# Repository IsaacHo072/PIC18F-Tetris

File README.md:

# PIC18F-Tetris
Tetris game which runs on a PIC18

## Hardware
- PIC18F4520
- HT16K33
- 8x8 Bi-Colour Common-Cathode LED Matrix
- 13mm Seven Segment Display, Common-Cathode
- 74HC14
- Some cherry-mx compatible switches

## Program
- Button polling used to read the buttons
- simpletetris.c is the main game program, also directly write to the displays
- Device configuration code in devcon.h

## Tetris
Has basic Tetris features including moving left, right, down and rotating the piece.
Also for holding one Tetris piece in top-left corner. Top-right corner shows the next piece to be dropped.

## Compiling
The program could be compiled with the legacy MPLAB C18 C Complier. 
Change the device configuration and I2C function to I2C1/2 if a different PIC18 microcontroller is used.

## Pictures

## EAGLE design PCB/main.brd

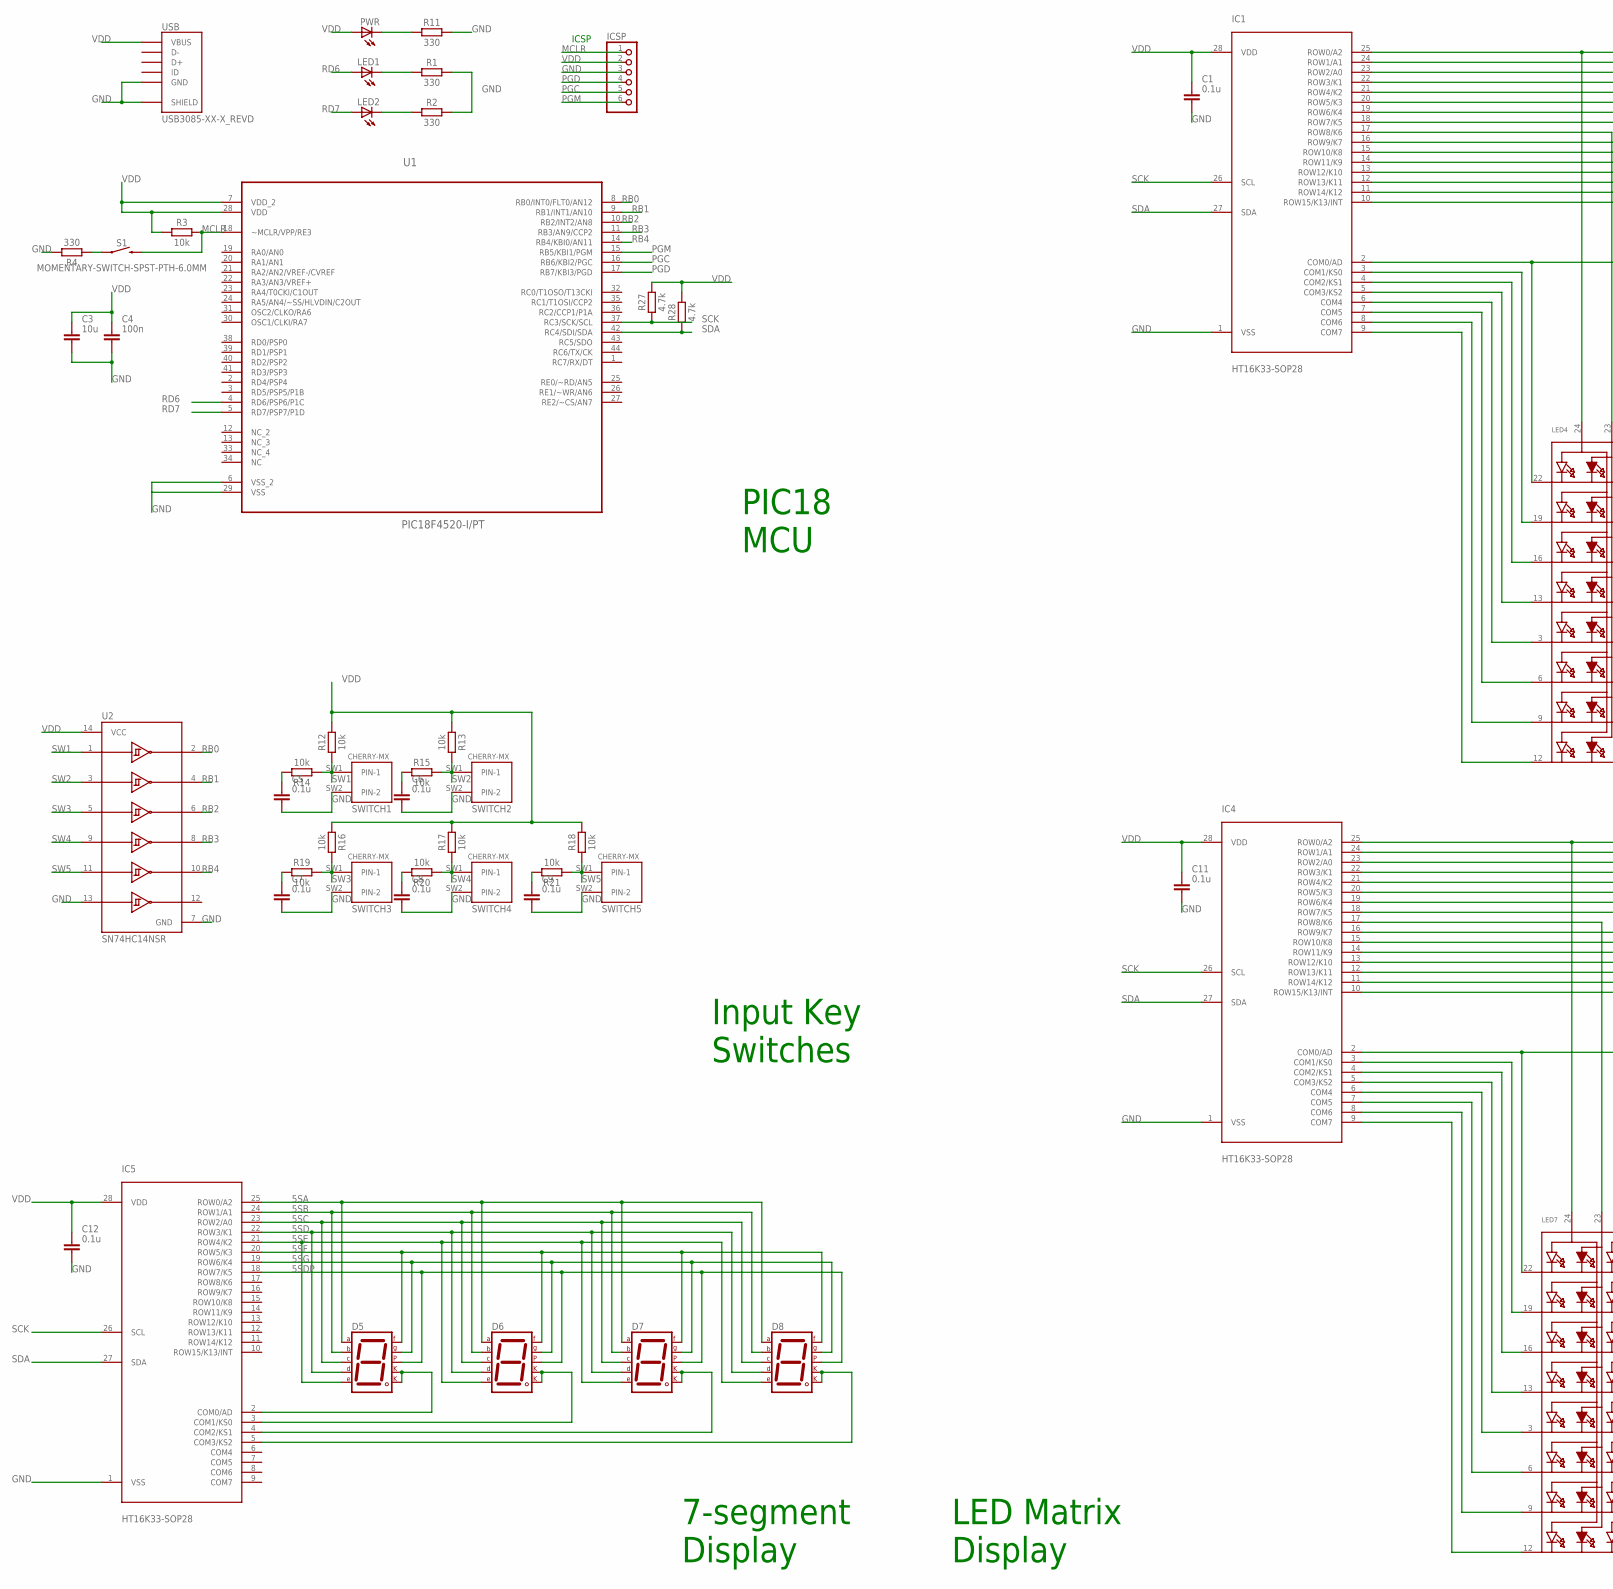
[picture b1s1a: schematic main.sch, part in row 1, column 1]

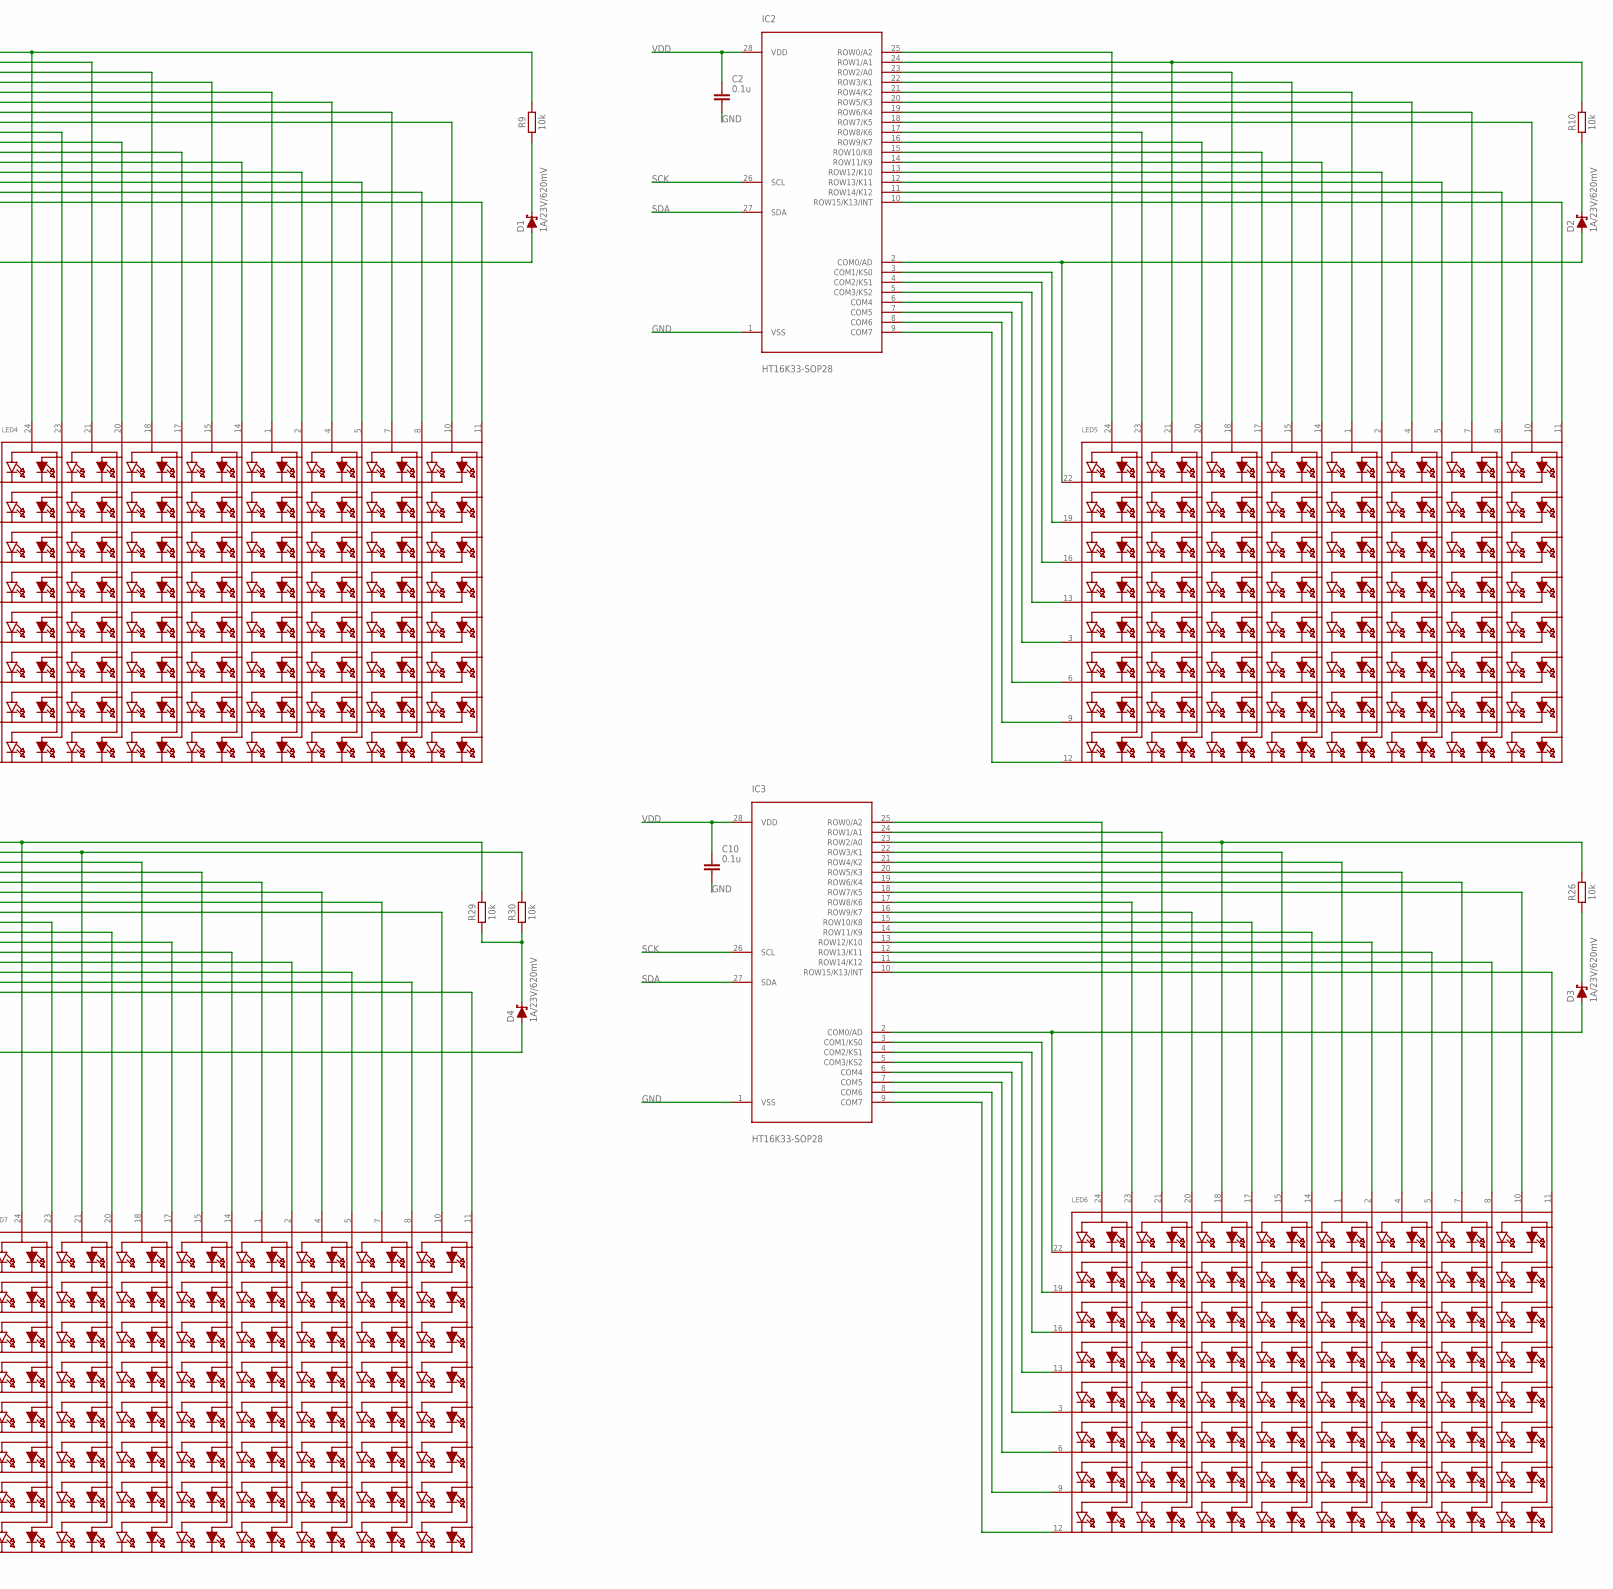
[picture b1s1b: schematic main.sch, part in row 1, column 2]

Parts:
C1, C2, C5, C6, C7, C8, C9, C10, C11, C12: 0.1u; CAPC2012X110
C3: 10u; CAPC2012X110
C4: 100n; CAPC2012X110
D1, D2, D3, D4: 1A/23V/620mV; SOD-323
D5, D6, D7, D8: 7SEG-CK; 7SEG-13
IC1, IC2, IC3, IC4, IC5: HT16K33-SOP28; SOIC127P1031X264-28N
ICSP: PINHD-1X6; 1X06
LED1, LED2: LEDCHIPLED_0805; CHIPLED_0805
LED4, LED5, LED6, LED7: SEGMENT_8X8_BICOLOR_ROWCATHODEMI2A883XX; SEGMENT_BICOL_BL-M12A883XX
PWR: LEDCHIPLED_0805; CHIPLED_0805
R1, R2, R4, R11: 330; RESC2012X65
R3, R9, R10, R12, R13, R14, R15, R16, R17, R18, R19, R20, R21, R26, R29, R30: 10k; RESC2012X65
R27, R28: 4.7k; RESC2012X65
S1: MOMENTARY-SWITCH-SPST-PTH-6.0MM; TACTILE_SWITCH_PTH_6.0MM
SWITCH1, SWITCH2, SWITCH3, SWITCH4, SWITCH5: CHERRY-MX
U1: PIC18F4520-I/PT; QFP80P1200X1200X120-44N
U2: SN74HC14NSR; SOP127P780X200-14N
USB: USB3085-XX-X_REVD; GCT_USB3085-XX-X_REVD

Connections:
5D2: D7.3 (CK1), D7.8 (CK2), IC5.4 (COM2/KS1)
5D3: D8.3 (CK1), D8.8 (CK2), IC5.5 (COM3/KS2)
5SA: D5.7 (A), D6.7 (A), D7.7 (A), D8.7 (A), IC5.25 (ROW0/A2)
5SB: D5.6 (B), D6.6 (B), D7.6 (B), D8.6 (B), IC5.24 (ROW1/A1)
5SC: D5.4 (C), D6.4 (C), D7.4 (C), D8.4 (C), IC5.23 (ROW2/A0)
5SD: D5.2 (D), D6.2 (D), D7.2 (D), D8.2 (D), IC5.22 (ROW3/K1)
5SDP: D5.5 (DP), D6.5 (DP), D7.5 (DP), D8.5 (DP), IC5.18 (ROW7/K5)
5SE: D5.1 (E), D6.1 (E), D7.1 (E), D8.1 (E), IC5.21 (ROW4/K2)
5SF: D5.9 (F), D6.9 (F), D7.9 (F), D8.9 (F), IC5.20 (ROW5/K3)
5SG: D5.10 (G), D6.10 (G), D7.10 (G), D8.10 (G), IC5.19 (ROW6/K4)
GND: C1.2, C2.2, C3.2, C4.2, C5.2, C6.2, C7.2, C8.2, C9.2, C10.2, C11.2, C12.2, IC1.1 (VSS), IC2.1 (VSS), IC3.1 (VSS), IC4.1 (VSS), IC5.1 (VSS), ICSP.3, R1.2, R2.2, R4.2, R11.1, SWITCH1.SW2 (PIN-2), SWITCH2.SW2 (PIN-2), SWITCH3.SW2 (PIN-2), SWITCH4.SW2 (PIN-2), SWITCH5.SW2 (PIN-2), U1.6 (VSS_2), U1.29 (VSS), U2.7 (GND), U2.13 (6A), USB.5 (GND), USB.6 (SHIELD), USB.7 (SHIELD), USB.8 (SHIELD), USB.9 (SHIELD)
MCLR: ICSP.1, R3.2, S1.3 (2), U1.18 (~MCLR/VPP/RE3)
unnamed: IC1.25 (ROW0/A2), LED4.24 (A1), R9.2
unnamed: IC1.24 (ROW1/A1), LED4.21 (A3)
unnamed: R4.1, S1.1
unnamed: IC1.23 (ROW2/A0), LED4.18 (A5)
unnamed: IC1.22 (ROW3/K1), LED4.15 (A7)
unnamed: IC1.21 (ROW4/K2), LED4.1 (A9)
unnamed: IC1.20 (ROW5/K3), LED4.4 (A11)
unnamed: IC1.19 (ROW6/K4), LED4.7 (A13)
unnamed: IC1.18 (ROW7/K5), LED4.10 (A15)
unnamed: IC1.17 (ROW8/K6), LED4.23 (A2)
unnamed: IC1.16 (ROW9/K7), LED4.20 (A4)
unnamed: IC1.15 (ROW10/K8), LED4.17 (A6)
unnamed: IC1.14 (ROW11/K9), LED4.14 (A8)
unnamed: IC1.13 (ROW12/K10), LED4.2 (A10)
unnamed: IC1.12 (ROW13/K11), LED4.5 (A12)
unnamed: IC1.11 (ROW14/K12), LED4.8 (A14)
unnamed: IC1.10 (ROW15/K13/INT), LED4.11 (A16)
unnamed: D1.A, IC1.2 (COM0/AD), LED4.22 (K1)
unnamed: IC1.3 (COM1/KS0), LED4.19 (K2)
unnamed: IC1.4 (COM2/KS1), LED4.16 (K3)
unnamed: IC1.5 (COM3/KS2), LED4.13 (K4)
unnamed: IC1.6 (COM4), LED4.3 (K5)
unnamed: IC1.7 (COM5), LED4.6 (K6)
unnamed: IC1.8 (COM6), LED4.9 (K7)
unnamed: IC1.9 (COM7), LED4.12 (K8)
unnamed: D1.C, R9.1
unnamed: C9.1, R21.2
unnamed: IC2.25 (ROW0/A2), LED5.24 (A1)
unnamed: IC2.24 (ROW1/A1), LED5.21 (A3), R10.2
unnamed: IC2.23 (ROW2/A0), LED5.18 (A5)
unnamed: IC2.22 (ROW3/K1), LED5.15 (A7)
unnamed: IC2.21 (ROW4/K2), LED5.1 (A9)
unnamed: IC2.20 (ROW5/K3), LED5.4 (A11)
unnamed: IC2.19 (ROW6/K4), LED5.7 (A13)
unnamed: IC2.18 (ROW7/K5), LED5.10 (A15)
unnamed: IC2.17 (ROW8/K6), LED5.23 (A2)
unnamed: IC2.16 (ROW9/K7), LED5.20 (A4)
unnamed: IC2.15 (ROW10/K8), LED5.17 (A6)
unnamed: IC2.14 (ROW11/K9), LED5.14 (A8)
unnamed: IC2.13 (ROW12/K10), LED5.2 (A10)
unnamed: IC2.12 (ROW13/K11), LED5.5 (A12)
unnamed: IC2.11 (ROW14/K12), LED5.8 (A14)
unnamed: IC2.10 (ROW15/K13/INT), LED5.11 (A16)
unnamed: D2.A, IC2.2 (COM0/AD), LED5.22 (K1)
unnamed: IC2.3 (COM1/KS0), LED5.19 (K2)
unnamed: IC2.4 (COM2/KS1), LED5.16 (K3)
unnamed: LED1.C, R1.1
unnamed: PWR.C, R11.2
unnamed: IC2.5 (COM3/KS2), LED5.13 (K4)
unnamed: IC2.6 (COM4), LED5.3 (K5)
unnamed: IC2.7 (COM5), LED5.6 (K6)
unnamed: IC2.8 (COM6), LED5.9 (K7)
unnamed: LED2.C, R2.1
unnamed: C5.1, R14.2
unnamed: C6.1, R15.1
unnamed: C8.1, R20.2
unnamed: C7.1, R19.1
unnamed: IC2.9 (COM7), LED5.12 (K8)
unnamed: D2.C, R10.1
unnamed: IC4.24 (ROW1/A1), LED7.21 (A3), R30.2
unnamed: IC4.23 (ROW2/A0), LED7.18 (A5)
unnamed: IC4.22 (ROW3/K1), LED7.15 (A7)
unnamed: IC4.21 (ROW4/K2), LED7.1 (A9)
unnamed: IC4.20 (ROW5/K3), LED7.4 (A11)
unnamed: IC4.19 (ROW6/K4), LED7.7 (A13)
unnamed: IC4.18 (ROW7/K5), LED7.10 (A15)
unnamed: IC4.17 (ROW8/K6), LED7.23 (A2)
unnamed: IC4.16 (ROW9/K7), LED7.20 (A4)
unnamed: IC4.15 (ROW10/K8), LED7.17 (A6)
unnamed: IC4.14 (ROW11/K9), LED7.14 (A8)
unnamed: IC4.13 (ROW12/K10), LED7.2 (A10)
unnamed: IC4.12 (ROW13/K11), LED7.5 (A12)
unnamed: IC4.11 (ROW14/K12), LED7.8 (A14)
unnamed: IC4.10 (ROW15/K13/INT), LED7.11 (A16)
unnamed: D4.A, IC4.2 (COM0/AD), LED7.22 (K1)
unnamed: IC4.3 (COM1/KS0), LED7.19 (K2)
unnamed: IC4.4 (COM2/KS1), LED7.16 (K3)
unnamed: IC4.5 (COM3/KS2), LED7.13 (K4)
unnamed: IC4.6 (COM4), LED7.3 (K5)
unnamed: IC4.7 (COM5), LED7.6 (K6)
unnamed: IC4.8 (COM6), LED7.9 (K7)
unnamed: IC4.9 (COM7), LED7.12 (K8)
unnamed: D4.C, R29.1, R30.1
unnamed: IC4.25 (ROW0/A2), LED7.24 (A1), R29.2
unnamed: IC3.25 (ROW0/A2), LED6.24 (A1)
unnamed: IC3.24 (ROW1/A1), LED6.21 (A3)
unnamed: IC3.23 (ROW2/A0), LED6.18 (A5), R26.2
unnamed: IC3.22 (ROW3/K1), LED6.15 (A7)
unnamed: IC3.21 (ROW4/K2), LED6.1 (A9)
unnamed: IC3.20 (ROW5/K3), LED6.4 (A11)
unnamed: IC3.19 (ROW6/K4), LED6.7 (A13)
unnamed: IC3.18 (ROW7/K5), LED6.10 (A15)
unnamed: IC3.17 (ROW8/K6), LED6.23 (A2)
unnamed: IC3.16 (ROW9/K7), LED6.20 (A4)
unnamed: IC3.15 (ROW10/K8), LED6.17 (A6)
unnamed: IC3.14 (ROW11/K9), LED6.14 (A8)
unnamed: IC3.13 (ROW12/K10), LED6.2 (A10)
unnamed: IC3.12 (ROW13/K11), LED6.5 (A12)
unnamed: IC3.11 (ROW14/K12), LED6.8 (A14)
unnamed: IC3.10 (ROW15/K13/INT), LED6.11 (A16)
unnamed: D3.A, IC3.2 (COM0/AD), LED6.22 (K1)
unnamed: IC3.3 (COM1/KS0), LED6.19 (K2)
unnamed: IC3.4 (COM2/KS1), LED6.16 (K3)
unnamed: IC3.5 (COM3/KS2), LED6.13 (K4)
unnamed: IC3.6 (COM4), LED6.3 (K5)
unnamed: IC3.7 (COM5), LED6.6 (K6)
unnamed: IC3.8 (COM6), LED6.9 (K7)
unnamed: IC3.9 (COM7), LED6.12 (K8)
unnamed: D3.C, R26.1
unnamed: D5.3 (CK1), D5.8 (CK2), IC5.2 (COM0/AD)
unnamed: D6.3 (CK1), D6.8 (CK2), IC5.3 (COM1/KS0)
PGC: ICSP.5, U1.16 (RB6/KBI2/PGC)
PGD: ICSP.4, U1.17 (RB7/KBI3/PGD)
PGM: ICSP.6, U1.15 (RB5/KBI1/PGM)
RB0: U1.8 (RB0/INT0/FLT0/AN12), U2.2 (1Y)
RB1: U1.9 (RB1/INT1/AN10), U2.4 (2Y)
RB2: U1.10 (RB2/INT2/AN8), U2.6 (3Y)
RB3: U1.11 (RB3/AN9/CCP2), U2.8 (4Y)
RB4: U1.14 (RB4/KBI0/AN11), U2.10 (5Y)
RD6: LED1.A, U1.4 (RD6/PSP6/P1C)
RD7: LED2.A, U1.5 (RD7/PSP7/P1D)
SCK: IC1.26 (SCL), IC2.26 (SCL), IC3.26 (SCL), IC4.26 (SCL), IC5.26 (SCL), R27.2, U1.37 (RC3/SCK/SCL)
SDA: IC1.27 (SDA), IC2.27 (SDA), IC3.27 (SDA), IC4.27 (SDA), IC5.27 (SDA), R28.2, U1.42 (RC4/SDI/SDA)
SW1: R12.1, R14.1, SWITCH1.SW1 (PIN-1), U2.1 (1A)
SW2: R13.2, R15.2, SWITCH2.SW1 (PIN-1), U2.3 (2A)
SW3: R16.2, R19.2, SWITCH3.SW1 (PIN-1), U2.5 (3A)
SW4: R17.1, R20.1, SWITCH4.SW1 (PIN-1), U2.9 (4A)
SW5: R18.1, R21.1, SWITCH5.SW1 (PIN-1), U2.11 (5A)
VDD: C1.1, C2.1, C3.1, C4.1, C10.1, C11.1, C12.1, IC1.28 (VDD), IC2.28 (VDD), IC3.28 (VDD), IC4.28 (VDD), IC5.28 (VDD), ICSP.2, PWR.A, R3.1, R12.2, R13.1, R16.1, R17.2, R18.2, R27.1, R28.1, U1.7 (VDD_2), U1.28 (VDD), U2.14 (VCC), USB.1 (VBUS)

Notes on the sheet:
ICSP
PIC18 MCU
Input Key Switches
7-segment Display
LED Matrix Display

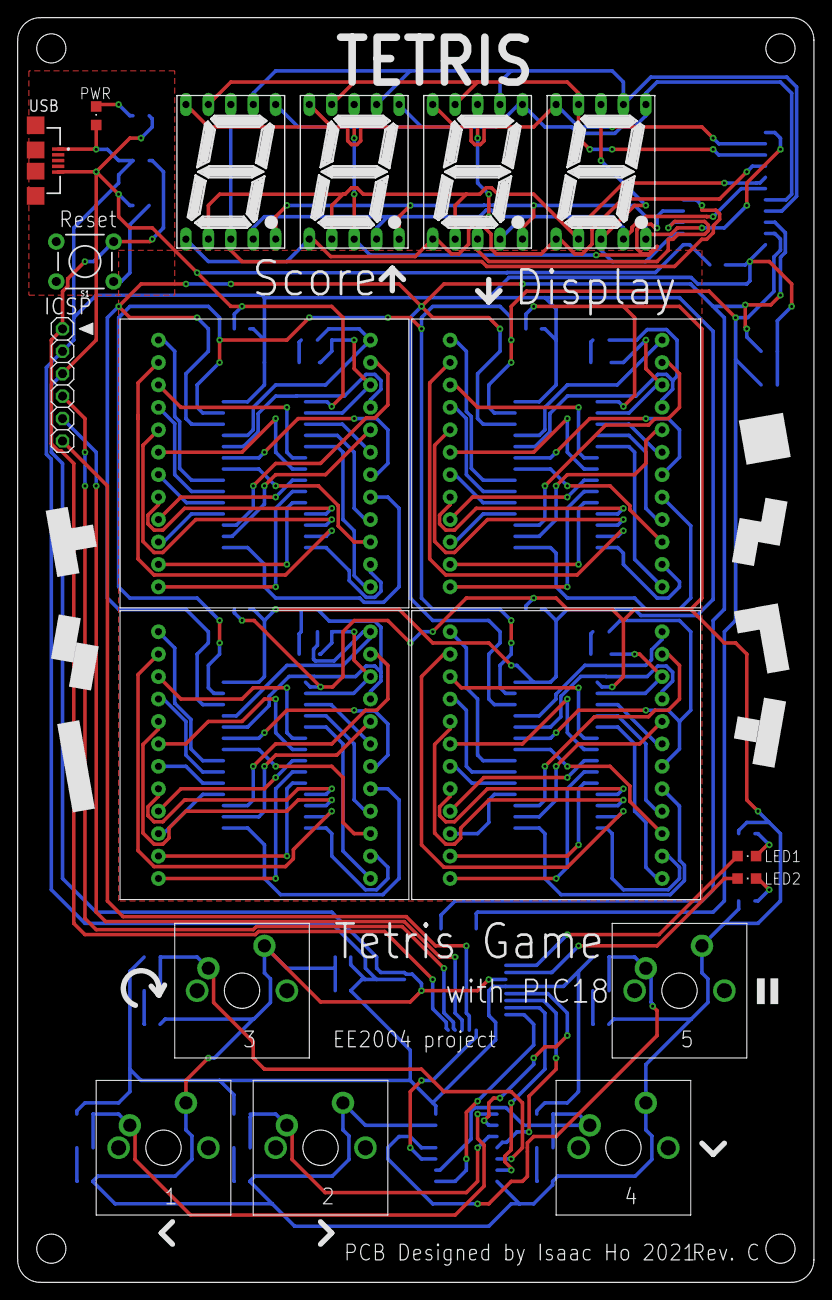
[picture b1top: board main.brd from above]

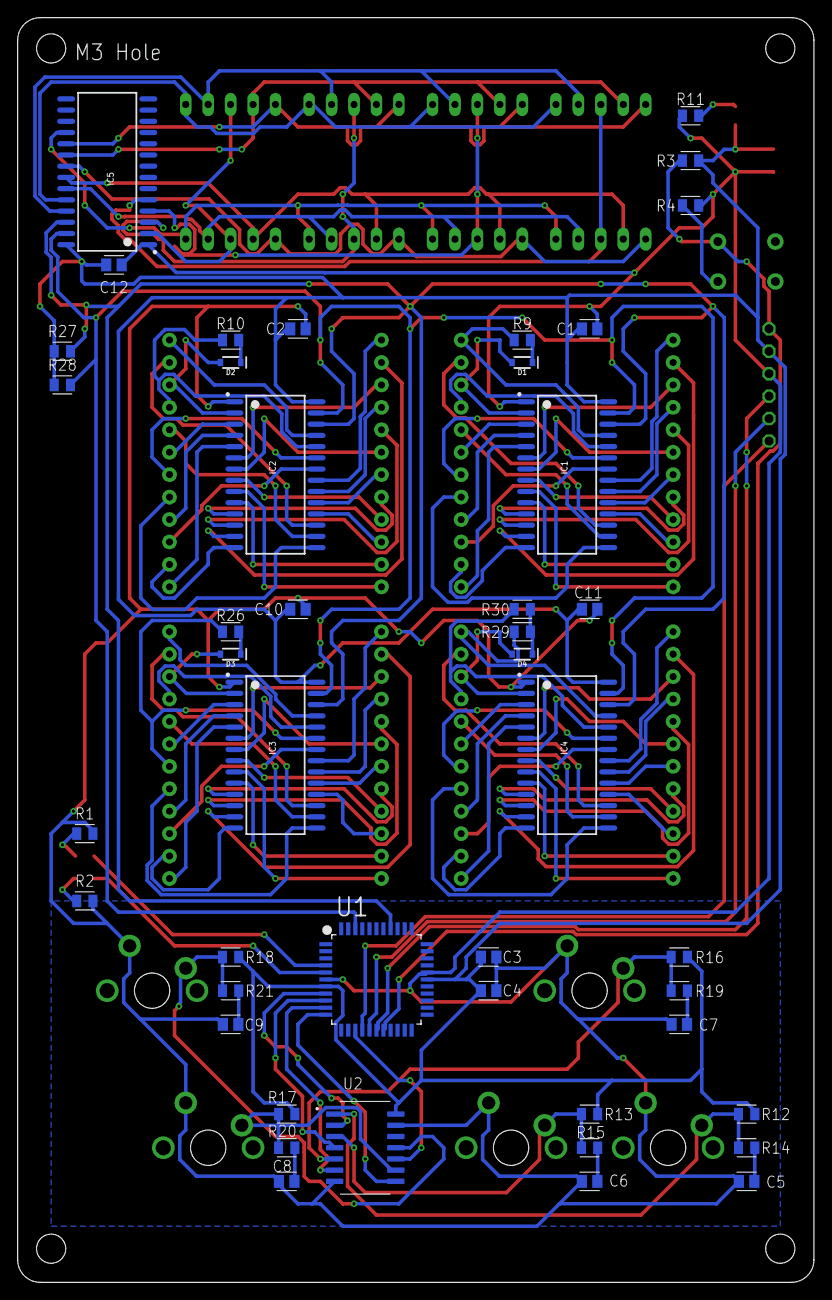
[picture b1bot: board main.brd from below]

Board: 2 copper layers, 90.2 x 143.2 mm, 64 parts (45 on the bottom side), 141 nets.

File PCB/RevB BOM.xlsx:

Bill of Materials
Part | Value | Device | Package | Description | Price - HKD
C1 | 0.1u | C_CHIP-0805 | 0805 | Capacitor | 0.16619999999999999
C2 | 0.1u | C_CHIP-0805 | 0805 | Capacitor | 0.16619999999999999
C3 | 10u | C_CHIP-0805 | 0805 | Capacitor | 0.2137
C4 | 0.1u | C_CHIP-0805 | 0805 | Capacitor | 0.16619999999999999
C5 | 0.1u | C_CHIP-0805 | 0805 | Capacitor | 0.16619999999999999
C6 | 0.1u | C_CHIP-0805 | 0805 | Capacitor | 0.16619999999999999
C7 | 0.1u | C_CHIP-0805 | 0805 | Capacitor | 0.16619999999999999
C8 | 0.1u | C_CHIP-0805 | 0805 | Capacitor | 0.16619999999999999
C9 | 0.1u | C_CHIP-0805 | 0805 | Capacitor | 0.16619999999999999
C10 | 0.1u | C_CHIP-0805 | 0805 | Capacitor | 0.16619999999999999
C11 | 0.1u | C_CHIP-0805 | 0805 | Capacitor | 0.16619999999999999
C12 | DNP
D1 | 1A/23V/620mV | DIODE-SCHOTTKY-BAT20J | SOD-323 | Schottky Diode | 8.6499999999999994E-2
D2 | 1A/23V/620mV | DIODE-SCHOTTKY-BAT20J | SOD-323 | Schottky Diode | 8.6499999999999994E-2
D3 | 1A/23V/620mV | DIODE-SCHOTTKY-BAT20J | SOD-323 | Schottky Diode | 8.6499999999999994E-2
D4 | 1A/23V/620mV | DIODE-SCHOTTKY-BAT20J | SOD-323 | Schottky Diode | 8.6499999999999994E-2
D5 |  | 7SEG-CK | 7SEG-13 | 7-segment Display | 0.60499999999999998
D6 |  | 7SEG-CK | 7SEG-13 | 7-segment Display | 0.60499999999999998
D7 |  | 7SEG-CK | 7SEG-13 | 7-segment Display | 0.60499999999999998
D8 |  | 7SEG-CK | 7SEG-13 | 7-segment Display | 0.60499999999999998
IC1 |  | HT16K33-SOP28 | SOIC127P1031X264-28N | RAM Mapping 16*8 LED Controller Driver | 6.41
IC2 |  | HT16K33-SOP28 | SOIC127P1031X264-28N | RAM Mapping 16*8 LED Controller Driver | 6.41
IC3 |  | HT16K33-SOP28 | SOIC127P1031X264-28N | RAM Mapping 16*8 LED Controller Driver | 6.41
IC4 |  | HT16K33-SOP28 | SOIC127P1031X264-28N | RAM Mapping 16*8 LED Controller Driver | 6.41
IC5 |  | HT16K33-SOP28 | SOIC127P1031X264-28N | RAM Mapping 16*8 LED Controller Driver | 6.41
ICSP |  | 1x6 Pin Header | 1x06 | Pin Header | 8.3000000000000004E-2
LED1 |  | LEDCHIP | 0805 |  | 0.1245
LED2 |  | LEDCHIP | 0805 |  | 0.1295
LED_PWR |  | LEDCHIP | 0805 |  | 0.14399999999999999
LED4 |  | 8x8 LED Segment | SEGMENT_BICOL_BL-M12A883XX | 8x8 Bi-Color LED Segment Displays: Row = Cathode | 61.82
LED5 |  | 8x8 LED Segment | SEGMENT_BICOL_BL-M12A883XX | 8x8 Bi-Color LED Segment Displays: Row = Cathode | 61.82
LED6 |  | 8x8 LED Segment | SEGMENT_BICOL_BL-M12A883XX | 8x8 Bi-Color LED Segment Displays: Row = Cathode | 61.82
LED7 |  | 8x8 LED Segment | SEGMENT_BICOL_BL-M12A883XX | 8x8 Bi-Color LED Segment Displays: Row = Cathode | 61.82
R1 | 330 | R_0805 | 0805 | Resistor | 4.1300000000000003E-2
R2 | 330 | R_0805 | 0805 | Resistor | 4.1300000000000003E-2
R3 | 10k | R_0805 | 0805 | Resistor | 4.1300000000000003E-2
R4 | 330 | R_0805 | 0805 | Resistor | 4.1300000000000003E-2
R5 | DNP
R6 | DNP
R7 | DNP
R8 | DNP
R9 | 10k | R_0805 | 0805 | Resistor | 4.1300000000000003E-2
R10 | 10k | R_0805 | 0805 | Resistor | 4.1300000000000003E-2
R11 | 330 | R_0805 | 0805 | Resistor | 4.1300000000000003E-2
R12 | 10k | R_0805 | 0805 | Resistor | 4.1300000000000003E-2
R13 | 10k | R_0805 | 0805 | Resistor | 4.1300000000000003E-2
R14 | 10k | R_0805 | 0805 | Resistor | 4.1300000000000003E-2
R15 | 10k | R_0805 | 0805 | Resistor | 4.1300000000000003E-2
R16 | 10k | R_0805 | 0805 | Resistor | 4.1300000000000003E-2
R17 | 10k | R_0805 | 0805 | Resistor | 4.1300000000000003E-2
R18 | 10k | R_0805 | 0805 | Resistor | 4.1300000000000003E-2
R19 | 10k | R_0805 | 0805 | Resistor | 4.1300000000000003E-2
R20 | 10k | R_0805 | 0805 | Resistor | 4.1300000000000003E-2
R21 | 10k | R_0805 | 0805 | Resistor | 4.1300000000000003E-2
R22 | DNP
R23 | DNP
R24 | DNP
R25 | DNP
R26 | 10K | R_0805 | 0805 | Resistor | 4.1300000000000003E-2
R27 | 4.7K | R_0805 | 0805 | Resistor | 4.1300000000000003E-2
R28 | 4.7K | R_0805 | 0805 | Resistor | 4.1300000000000003E-2
R29 | 10K | R_0805 | 0805 | Resistor | 4.1300000000000003E-2
R30 | 10K | R_0805 | 0805 | Resistor | 4.1300000000000003E-2
S1 |  | SPST Switch 6mm | TACTILE_SWITCH_PTH_6.0MM | Push Button | 4.9799999999999997E-2
SWITCH1 |  | Cherry MX Switch |  | Cherry MX Series Keyswitch | 1.163
SWITCH2 |  | Cherry MX Switch |  | Cherry MX Series Keyswitch | 1.163
SWITCH3 |  | Cherry MX Switch |  | Cherry MX Series Keyswitch | 1.163
SWITCH4 |  | Cherry MX Switch |  | Cherry MX Series Keyswitch | 1.163
SWITCH5 |  | Cherry MX Switch |  | Cherry MX Series Keyswitch | 1.163
U1 |  | PIC18F4520-I/PT | QFP80P1200X1200X120-44N | Flash Microcontrollers | 15.42
U2 |  | SN74HC14NSR | SOP127P780X200-14N | Hex Schmitt-Trigger Inverters | 1.0620000000000001
USB |  | USB3085-XX-X_RevD | GCT_USB3085-XX-X_REVD | Micro USB Receptacle, Type AB, Surface Mount, Horizontak, Bottom Mount, Without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 | 0.498
 | PCB |  |  |  | 22.956
 |  |  |  | Total | 331.16209999999961

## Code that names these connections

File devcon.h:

#ifndef DEVCON
#define DEVCON

#include <stdlib.h>
#include <math.h>
#include <i2c.h>
#include <delays.h>
#include <timers.h>

#include "simpletetris.h"
#include "ht16k33.h"
#include "helper.h"

#pragma config OSC = INTIO67
#pragma config WDT = OFF
#pragma config LVP = ON
#pragma config PBADEN = OFF

//LED1, LED2
#define LED1 PORTDbits.RD6
#define LED2 PORTDbits.RD7
//Buttons
#define ButtonLeft PORTBbits.RB0
#define ButtonRight PORTBbits.RB1
#define ButtonRotate PORTBbits.RB2
#define ButtonDown PORTBbits.RB3
#define ButtonHold PORTBbits.RB4


void DeviceSetup(void)
{
	//Use Internal Oscillator at 8MHz
	OSCCON = 0x72;
	OSCTUNE = 0x00;
	SSPADD = 0x04;

	//Ports Setup
	LATA = 0x00;
	LATB = 0x00;
	LATC = 0x00;
	LATD = 0x00;
	
	TRISA = 0xFF;
	TRISB = 0xFF;
	TRISC = 0xFF;
	TRISD = 0x3F;
	
	//Timer for 1s (around 1s)
	OpenTimer0(T0_16BIT & T0_SOURCE_INT & T0_PS_1_256);
	WriteTimer0(24954);
}

#endif

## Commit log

2021-05-01 Create 123
2021-05-01 Moving files
2021-05-01 Add PCB files
2021-05-01 add pictures and enclosure
2021-05-01 Uploaded simpletetris.hex
2021-05-01 Added STL files
2021-05-01 Added More Pictures
2021-05-01 Added Hex File
2021-05-01 Added BOM

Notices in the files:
parts and their libraries:
SparkFun-DiscreteSemi: Licensing: Creative Commons ShareAlike 4.0 International - https://creativecommons.org/licenses/by-sa/4.0
